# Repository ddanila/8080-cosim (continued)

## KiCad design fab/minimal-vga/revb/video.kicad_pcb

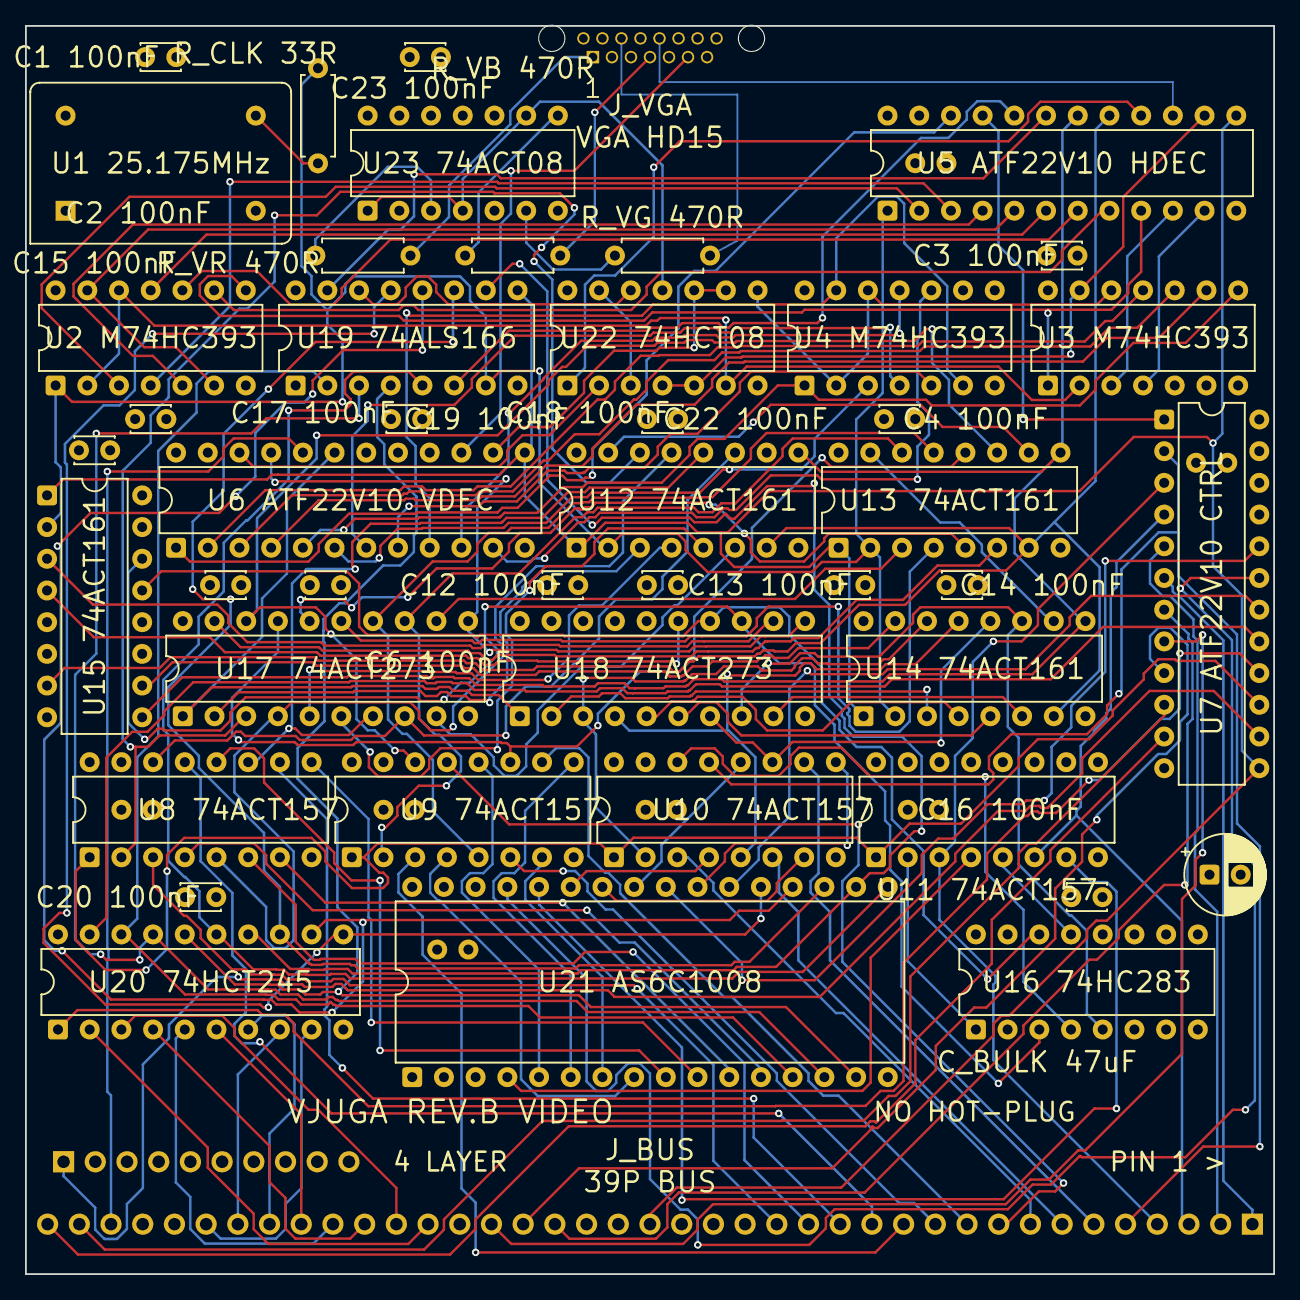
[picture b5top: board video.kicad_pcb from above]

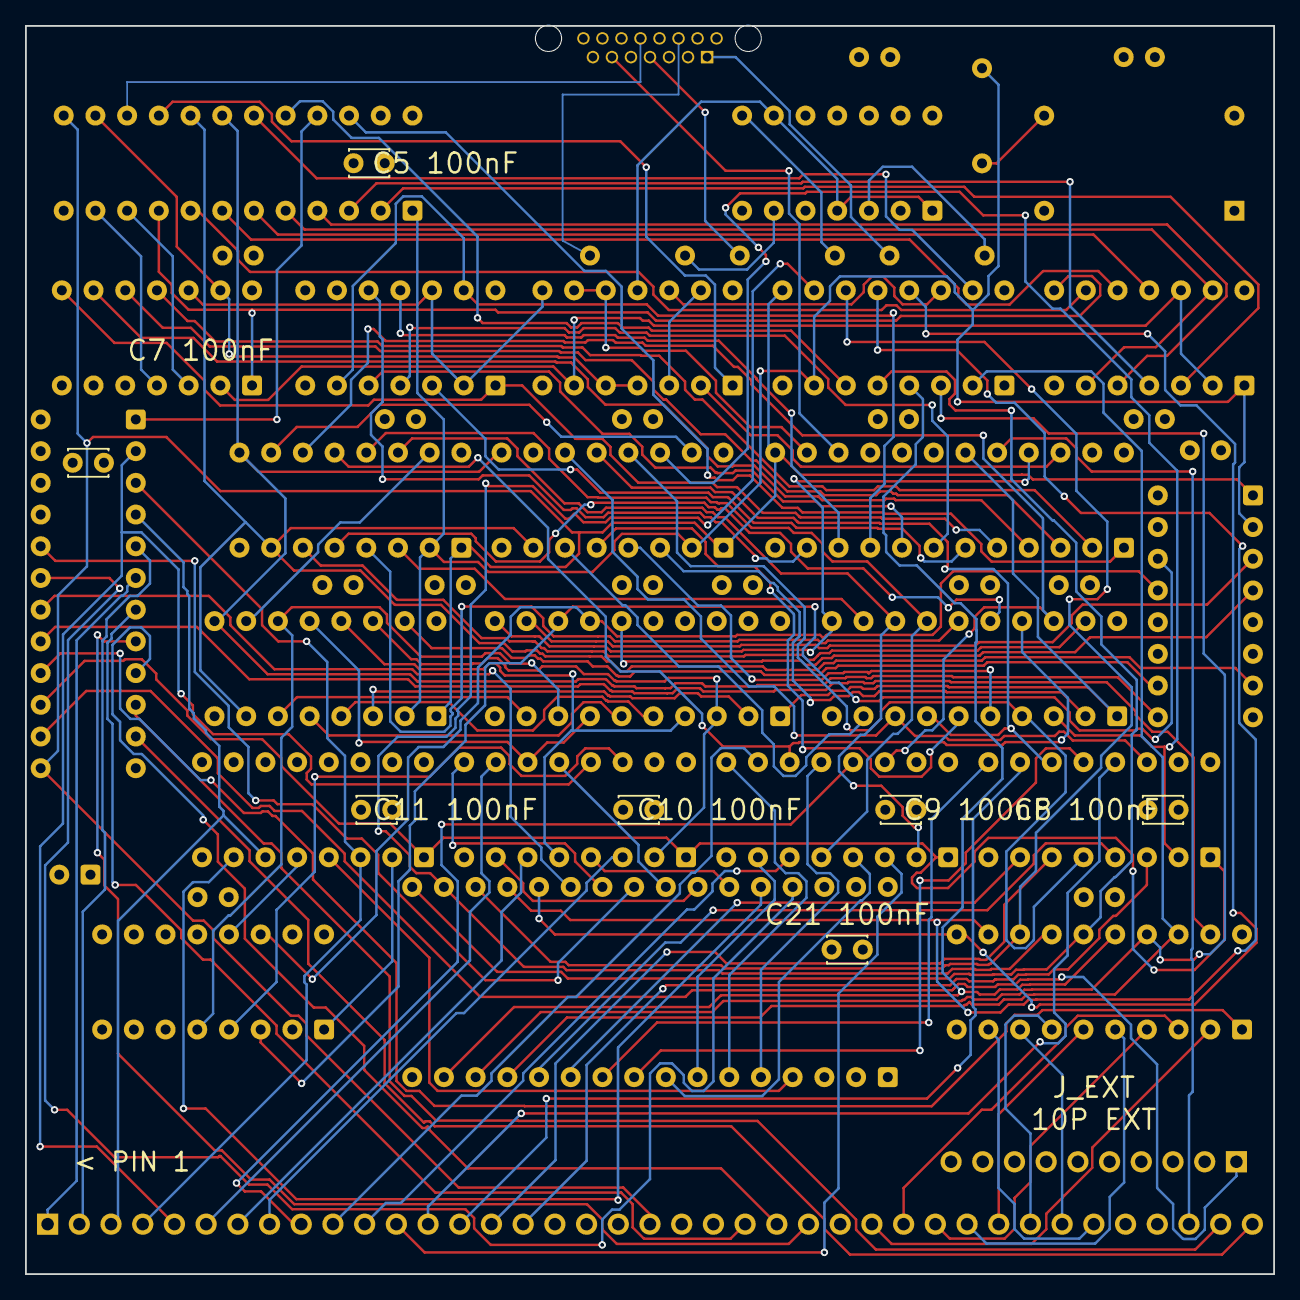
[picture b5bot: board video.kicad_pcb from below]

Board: 4 copper layers, 100.0 x 100.0 mm, 54 parts (8 on the bottom side), 143 nets.

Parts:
C1, C2, C3, C4, C5, C6, C7, C8, C9, C10, C11, C12, C13, C14, C15, C16, C17, C18, C19, C20, C21, C22, C23: C_Disc_D3.0mm_W2.0mm_P2.50mm
C_BULK: CP_Radial_D6.3mm_P2.50mm
J_BUS: PinHeader_1x39_P2.54mm_Horizontal
J_EXT: PinHeader_1x10_P2.54mm_Horizontal
J_VGA: NorComp_200-015-213L537
R_CLK: R_Axial_DIN0207_L6.3mm_D2.5mm_P7.62mm_Horizontal
R_VB: R_Axial_DIN0207_L6.3mm_D2.5mm_P7.62mm_Horizontal
R_VG: R_Axial_DIN0207_L6.3mm_D2.5mm_P7.62mm_Horizontal
R_VR: R_Axial_DIN0207_L6.3mm_D2.5mm_P7.62mm_Horizontal
U1: Oscillator_DIP-14
U2, U3, U4, U22, U23: DIP-14_W7.62mm
U5, U6, U7: DIP-24_W7.62mm
U8, U9, U10, U11, U12, U13, U14, U15, U16, U19: DIP-16_W7.62mm
U17, U18, U20: DIP-20_W7.62mm
U21: DIP-32_W15.24mm

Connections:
A0: J_BUS.16, U8.3
A1: J_BUS.15, U8.6
A2: J_BUS.14, U8.10
A3: J_BUS.13, U8.13
A4: J_BUS.12, U9.3
A5: J_BUS.11, U9.6
A6: J_BUS.10, U9.10
A7: J_BUS.9, U9.13
A8: J_BUS.8, U10.3
A9: J_BUS.7, U10.6
A10: J_BUS.6, U10.10
A11: J_BUS.5, U7.2, U10.13
A12: J_BUS.4, U7.3, U11.3
A13: J_BUS.3, U7.4, U11.6
A14: J_BUS.2, U7.5
A15: J_BUS.1, U7.6
BYTE_TICK: U5.17, U12.7, U13.7, U14.7, U15.7
D0: J_BUS.27, U20.2
D1: J_BUS.28, U20.3
D2: J_BUS.29, U20.4
D3: J_BUS.30, U20.5
D4: J_BUS.31, U20.6
D5: J_BUS.32, U20.7
D6: J_BUS.33, U20.8
D7: J_BUS.34, U20.9
D245_DIR: U7.16, U20.1
D245_OE: U7.17, U20.19
DOTCLK: R_CLK.2, U2.1, U5.1, U12.2, U13.2, U14.2, U15.2, U19.7
DOTCLK_RAW: R_CLK.1, U1.8
FBA11: U10.14, U16.4
FBA12: U11.2, U16.1
FBA13: U11.5, U16.13
FB_CE_N: U7.18, U21.22
FB_OE_N: U7.20, U21.24
FB_WE_N: U7.19, U21.29
FD0: U19.2, U20.18, U21.13
FD1: U19.3, U20.17, U21.14
FD2: U19.4, U20.16, U21.15
FD3: U19.5, U20.15, U21.17
FD4: U19.10, U20.14, U21.18
FD5: U19.11, U20.13, U21.19
FD6: U19.12, U20.12, U21.20
FD7: U19.13, U20.11, U21.21
FETCH: U5.21, U7.1
FI_LOAD_N: U5.18, U12.9, U13.9, U14.9, U15.9
FRAME_TICK: J_BUS.37, U6.20
FRAME_TOP_N: U6.19, U17.1, U18.1
GND: C1.2, C2.2, C3.2, C4.2, C5.2, C6.2, C7.2, C8.2, C9.2, C10.2, C11.2, C12.2, C13.2, C14.2, C15.2, C16.2, C17.2, C18.2, C19.2, C20.2, C21.2, C22.2, C23.2, C_BULK.2, J_BUS.17, J_EXT.10, J_VGA.5, J_VGA.6, J_VGA.7, J_VGA.8, J_VGA.10, U1.7, U2.7, U3.7, U4.7, U5.12, U6.12, U7.12, U8.8, U8.15, U9.8, U9.15, U10.8, U10.15, U11.8, U11.10, U11.11, U11.13, U11.14, U11.15, U12.8, U13.8, U14.8, U15.5, U15.6, U15.8, U16.7, U16.8, U16.11, U16.12, U16.15, U17.10, U18.10, U18.17, U18.18, U19.1, U19.8, U20.10, U21.2, U21.3, U21.16, U21.31, U22.7, U23.7, U23.12, U23.13
HC0: U2.3, U5.2
HC1: U2.4, U5.3
HC2: U2.5, U5.4
HC3: U2.6, U2.13, U5.5
HC4: U2.11, U5.6
HC5: U2.10, U5.7
HC6: U2.9, U5.8
HC7: U2.8, U3.1, U5.9
HC8: U3.3, U5.10
HC9: U3.4, U5.11
HSYNC_N: J_VGA.13, U5.15
HV_ACTIVE: U22.3, U22.13
H_ACTIVE: U5.16, U22.1
H_CLR: U2.2, U2.12, U3.2, U22.6
H_END: U3.13, U5.14, U22.4, U22.5
MODE0: J_BUS.38, U7.10
MODE1: J_BUS.39, U7.11
MREQ_N: J_BUS.23, U7.7
MUX_SEL: U7.15, U8.1, U9.1, U10.1, U11.1
PIXEL: U19.14, U22.12
RB0: U12.3, U17.2
RB1: U12.4, U17.5
RB2: U12.5, U17.6
RB3: U12.6, U17.9
RB4: U13.3, U17.12
RB5: U13.4, U17.15
RB6: U13.5, U17.16
RB7: U13.6, U17.19
RB8: U14.3, U18.2
RB9: U14.4, U18.5
RB10: U14.5, U18.6
RB11: U14.6, U18.9
RB12: U15.3, U18.12
RB13: U15.4, U18.15
RB_CLK: U6.21, U17.11, U18.11
RB_STROBE: U5.22, U6.1
RD_N: J_BUS.25, U7.8
RESET_N: J_BUS.20, U5.13, U6.13, U7.13, U12.1, U13.1, U14.1, U15.1, U19.9
SA0: U8.4, U21.12
SA1: U8.7, U21.11
SA2: U8.9, U21.10
SA3: U8.12, U21.9
SA4: U9.4, U21.8
SA5: U9.7, U21.7
SA6: U9.9, U21.6
SA7: U9.12, U21.5
SA8: U10.4, U21.27
SA9: U10.7, U21.26
SA10: U10.9, U21.23
SA11: U10.12, U21.25
SA12: U11.4, U21.4
SA13: U11.7, U21.28
SI0: U8.2, U12.14, U17.3
SI1: U8.5, U12.13, U17.4
SI2: U8.11, U12.12, U17.7
SI3: U8.14, U12.11, U17.8
SI4: U9.2, U13.14, U17.13
SI5: U9.5, U13.13, U17.14
SI6: U9.11, U13.12, U17.17
SI7: U9.14, U13.11, U17.18
SI8: U10.2, U14.14, U18.3
SI9: U10.5, U14.13, U18.4
SI10: U10.11, U14.12, U18.7
SI11: U14.11, U16.5, U18.8
SI12: U15.14, U16.3, U18.13
SI13: U15.13, U16.14, U18.14
SI_TC0: U12.15, U13.10
SI_TC1: U13.15, U14.10
SI_TC2: U14.15, U15.10
SR_INH: U5.20, U19.6
SR_LOAD_N: U5.19, U19.15
VC0: U3.11, U6.2
VC1: U3.10, U6.3
VC2: U3.9, U6.4
VC3: U3.8, U4.1, U6.5
VC4: U4.3, U6.6
VC5: U4.4, U6.7
VC6: U4.5, U6.8
VC7: U4.6, U4.13, U6.9
VC8: U4.11, U6.10
VC9: U4.10, U6.11
VCC5: C1.1, C2.1, C3.1, C4.1, C5.1, C6.1, C7.1, C8.1, C9.1, C10.1, C11.1, C12.1, C13.1, C14.1, C15.1, C16.1, C17.1, C18.1, C19.1, C20.1, C21.1, C22.1, C23.1, C_BULK.1, J_BUS.18, J_EXT.9, U1.14, U2.14, U3.14, U4.14, U5.24, U6.24, U7.24, U8.16, U9.16, U10.16, U11.16, U12.10, U12.16, U13.16, U14.16, U15.16, U16.2, U16.6, U16.16, U17.20, U18.20, U19.16, U20.20, U21.30, U21.32, U22.14, U23.2, U23.5, U23.10, U23.14
VID_B: J_VGA.3, R_VB.2
VID_B_DRV: R_VB.1, U23.8
VID_G: J_VGA.2, R_VG.2
VID_G_DRV: R_VG.1, U23.6
VID_PIXEL: U22.11, U23.1, U23.4, U23.9
VID_R: J_VGA.1, R_VR.2
VID_R_DRV: R_VR.1, U23.3
VSYNC_N: J_VGA.14, U6.15
V_ACTIVE: U6.22, U22.2
V_CLR: U3.12, U4.2, U4.12, U22.8
V_END: U6.14, U22.9, U22.10
WAIT_N: J_EXT.1, U7.14
WR_N: J_BUS.24, U7.9

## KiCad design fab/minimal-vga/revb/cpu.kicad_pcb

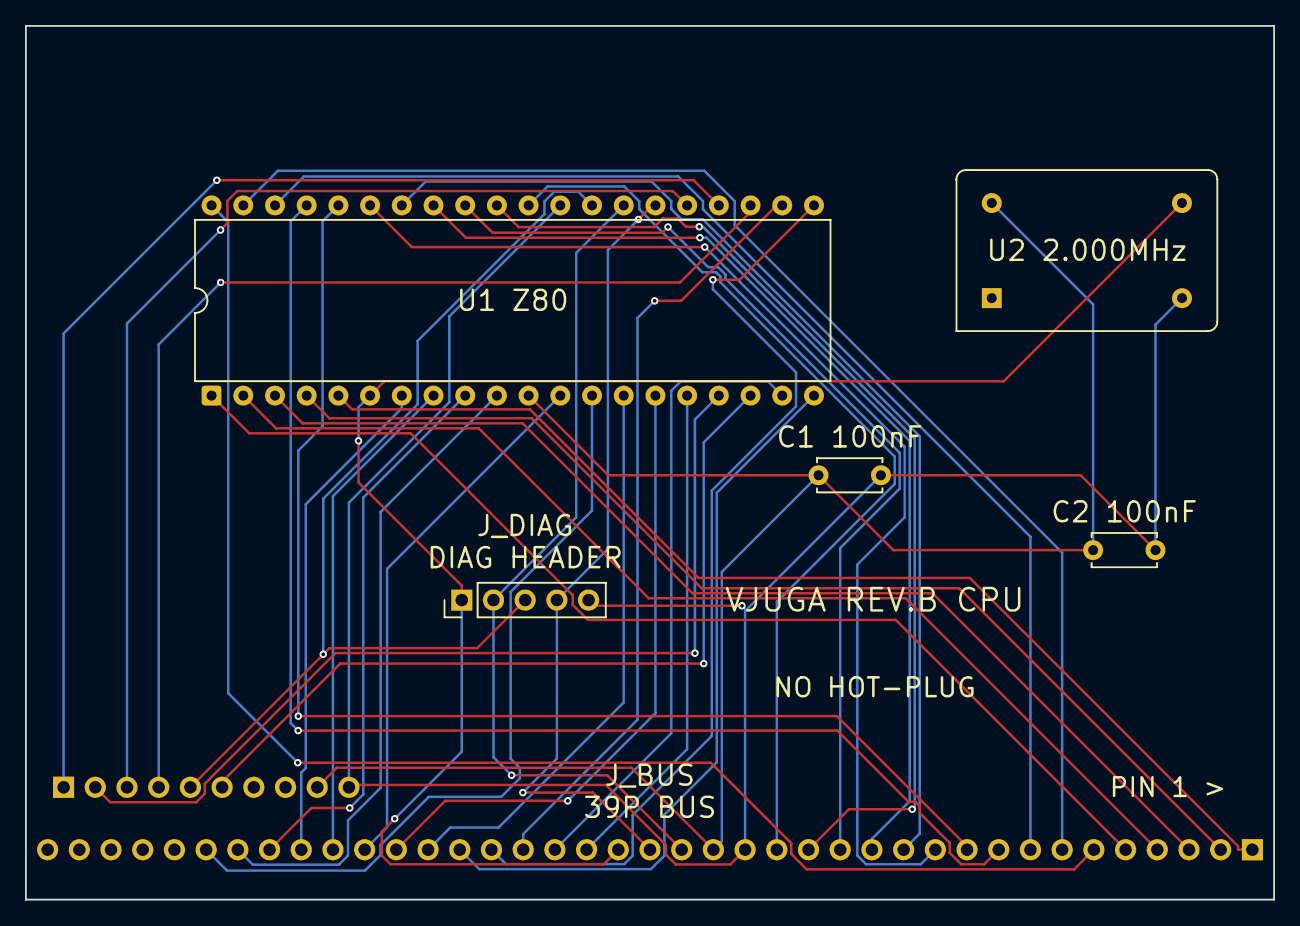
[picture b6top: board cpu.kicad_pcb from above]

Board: 2 copper layers, 100.0 x 70.0 mm, 7 parts (1 on the bottom side), 40 nets.

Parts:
C1, C2: C_Disc_D5.0mm_W2.5mm_P5.00mm
J_BUS: PinHeader_1x39_P2.54mm_Horizontal
J_DIAG: PinHeader_1x05_P2.54mm_Vertical
J_EXT: PinHeader_1x10_P2.54mm_Horizontal
U1: DIP-40_W15.24mm
U2: Oscillator_DIP-14

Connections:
A0: J_BUS.16, U1.30
A1: J_BUS.15, U1.31
A2: J_BUS.14, U1.32
A3: J_BUS.13, U1.33
A4: J_BUS.12, U1.34
A5: J_BUS.11, U1.35
A6: J_BUS.10, U1.36
A7: J_BUS.9, U1.37
A8: J_BUS.8, U1.38
A9: J_BUS.7, U1.39
A10: J_BUS.6, U1.40
A11: J_BUS.5, U1.1
A12: J_BUS.4, U1.2
A13: J_BUS.3, U1.3
A14: J_BUS.2, U1.4
A15: J_BUS.1, U1.5
BUSAK_N: J_EXT.4, U1.23
BUSRQ_N: J_EXT.3, U1.25
CLK: J_BUS.21, J_DIAG.1, U1.6, U2.8
D0: J_BUS.27, U1.14
D1: J_BUS.28, U1.15
D2: J_BUS.29, U1.12
D3: J_BUS.30, U1.8
D4: J_BUS.31, U1.7
D5: J_BUS.32, U1.9
D6: J_BUS.33, U1.10
D7: J_BUS.34, U1.13
GND: C1.2, C2.2, J_BUS.17, J_DIAG.5, J_EXT.10, U1.29, U2.7
HALT_N: J_EXT.6, U1.18
INT_N: J_BUS.22, U1.16
IORQ_N: J_BUS.26, U1.20
M1_N: J_BUS.19, J_DIAG.2, U1.27
MREQ_N: J_BUS.23, U1.19
NMI_N: J_EXT.2, U1.17
RD_N: J_BUS.25, U1.21
RESET_N: J_BUS.20, J_DIAG.4, U1.26
RFSH_N: J_DIAG.3, J_EXT.5, U1.28
VCC5: C1.1, C2.1, J_BUS.18, J_EXT.9, U1.11, U2.14
WAIT_N: J_EXT.1, U1.24
WR_N: J_BUS.24, U1.22

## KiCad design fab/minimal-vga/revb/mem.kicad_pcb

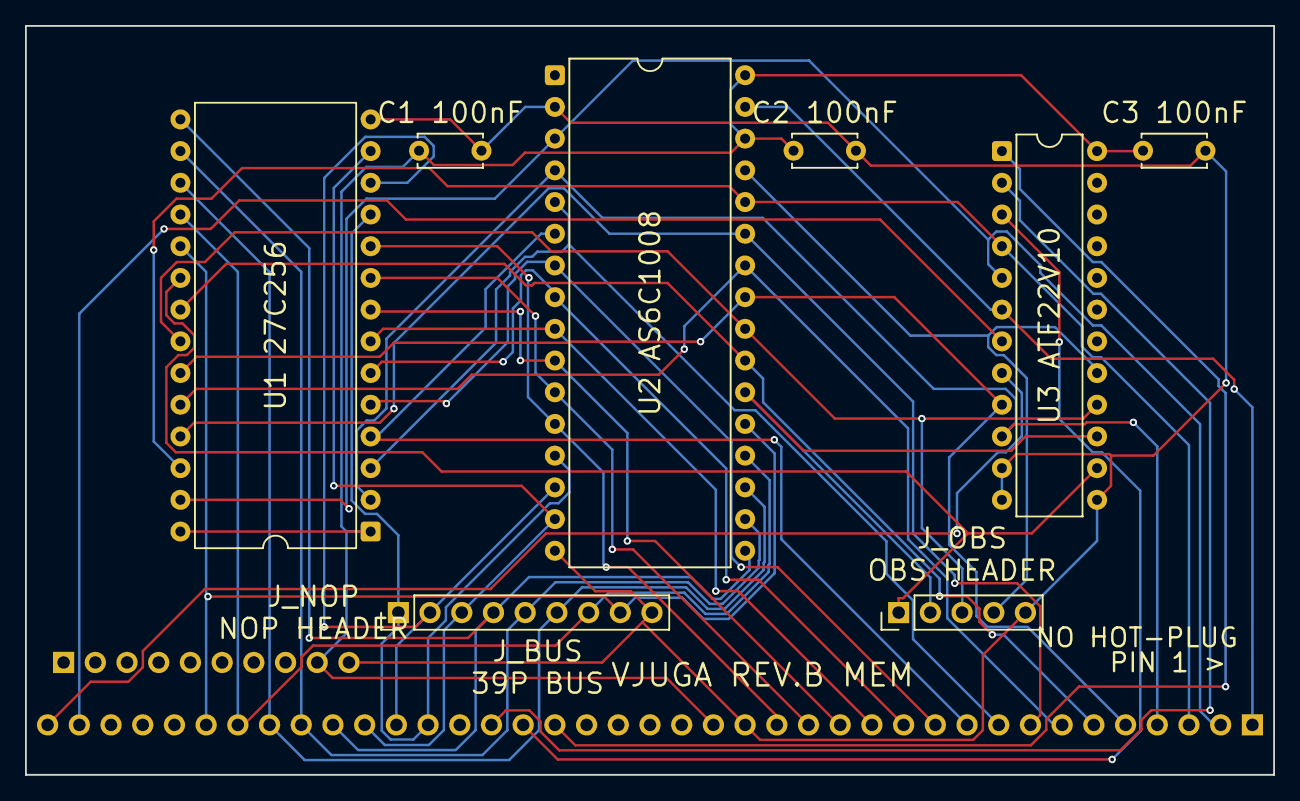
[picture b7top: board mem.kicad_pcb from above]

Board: 2 copper layers, 100.0 x 60.0 mm, 10 parts (1 on the bottom side), 35 nets.

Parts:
C1, C2, C3: C_Disc_D5.0mm_W2.5mm_P5.00mm
J_BUS: PinHeader_1x39_P2.54mm_Horizontal
J_EXT: PinHeader_1x10_P2.54mm_Horizontal
J_NOP: PinHeader_1x09_P2.54mm_Vertical
J_OBS: PinHeader_1x05_P2.54mm_Vertical
U1: DIP-28_W15.24mm
U2: DIP-32_W15.24mm
U3: DIP-24_W7.62mm

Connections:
A0: J_BUS.16, U1.10, U2.12
A1: J_BUS.15, U1.9, U2.11
A2: J_BUS.14, U1.8, U2.10
A3: J_BUS.13, U1.7, U2.9
A4: J_BUS.12, U1.6, U2.8
A5: J_BUS.11, U1.5, U2.7
A6: J_BUS.10, U1.4, U2.6
A7: J_BUS.9, U1.3, U2.5
A8: J_BUS.8, U1.25, U2.27
A9: J_BUS.7, U1.24, U2.26
A10: J_BUS.6, U1.21, U2.23
A11: J_BUS.5, U1.23, U2.25, U3.9
A12: J_BUS.4, U1.2, U2.4, U3.10
A13: J_BUS.3, U1.26, U2.28, U3.4
A14: J_BUS.2, U1.27, U2.3, U3.5
A15: J_BUS.1, U2.31, U3.6
D0: J_BUS.27, J_NOP.1, U1.11, U2.13
D1: J_BUS.28, J_NOP.2, U1.12, U2.14
D2: J_BUS.29, J_NOP.3, U1.13, U2.15
D3: J_BUS.30, J_NOP.4, U1.15, U2.17
D4: J_BUS.31, J_NOP.5, U1.16, U2.18
D5: J_BUS.32, J_NOP.6, U1.17, U2.19
D6: J_BUS.33, J_NOP.7, U1.18, U2.20
D7: J_BUS.34, J_NOP.8, U1.19, U2.21
GND: C1.2, C2.2, C3.2, J_BUS.17, J_EXT.10, J_NOP.9, J_OBS.5, U1.14, U2.2, U2.16, U3.11, U3.12, U3.13
MEM_RD_N: J_OBS.3, U1.22, U2.24, U3.16
MEM_WR_N: J_OBS.4, U2.29, U3.17
MODE0: J_BUS.38, U3.7
MODE1: J_BUS.39, U3.8
MREQ_N: J_BUS.23, U3.1
RAM_CE_N: J_OBS.2, U2.22, U3.15
RD_N: J_BUS.25, U3.2
ROM_CE_N: J_OBS.1, U1.20, U3.14
VCC5: C1.1, C2.1, C3.1, J_BUS.18, J_EXT.9, U1.1, U1.28, U2.30, U2.32, U3.24
WR_N: J_BUS.24, U3.3

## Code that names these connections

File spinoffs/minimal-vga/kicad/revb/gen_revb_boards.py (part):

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mating = json.loads((HERE / "mating.json").read_text())

# ---- accurate DIP pinouts (pin number -> net/function) ----
# Z80 DIP-40: transcribed verbatim from spinoffs/minimal-vga/kicad/rev-a-physical.board.json U1
# (rev A's authoritative Z80 mapping). BUSACK_N/NMI_N map to the rev B bus names.
Z80 = {
    "1":"A11","2":"A12","3":"A13","4":"A14","5":"A15","6":"CLK","7":"D4","8":"D3",
    "9":"D5","10":"D6","11":"VCC5","12":"D2","13":"D7","14":"D0","15":"D1","16":"INT_N",
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    "25":"A8","26":"A13","27":"A14","28":"VCC5",
}
# AS6C1008 DIP-32 (128K x 8 SRAM), Alliance Memory datasheet pinout.  Pin 1 is
# NC; pin 30 is the active-HIGH CE2.  The rev-B Memory card uses A0..A15, holds
# A16 low, and holds CE2 high.
SRAM_128K = {
    "1":"RAM_PIN1_NC","2":"GND","3":"A14","4":"A12","5":"A7","6":"A6","7":"A5","8":"A4",
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
# --- B3-tier parts (D1.26): footprinted AND fully wired on the io card, but DNP so
# B3 is populate-only, no respin. ---
# 82C55 PPI DIP-40. PA0-7 = keyboard columns; PB0-3 <- 74148 encoder; PC0/PC1 = the
# memory-overlay mode bits (bus MODE0/MODE1). Ports 0x04-0x07 via PPI_CS_N.
PPI_8255 = {
    "1":"KBD_COL3","2":"KBD_COL2","3":"KBD_COL1","4":"KBD_COL0","5":"RD_N","6":"PPI_CS_N",
    "7":"GND","8":"A1","9":"A0","10":"PC7_NC","11":"PC6_NC","12":"PC5_NC","13":"PC4_NC",
    "14":"MODE0","15":"MODE1","16":"PC2_NC","17":"PC3_NC",
    "18":"KBD_ENC0","19":"KBD_ENC1","20":"KBD_ENC2","21":"KBD_ENC_GS",
    "22":"PB4_NC","23":"PB5_NC","24":"PB6_NC","25":"PB7_NC","26":"VCC5",
    "27":"D7","28":"D6","29":"D5","30":"D4","31":"D3","32":"D2","33":"D1","34":"D0",
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ENC_74148 = {
    "1":"KBD_ROW4","2":"KBD_ROW5","3":"KBD_ROW6","4":"KBD_ROW7","5":"KBD_ENC_GS","6":"KBD_ENC2",
    "7":"KBD_ENC1","8":"GND","9":"KBD_ENC0","10":"KBD_ROW0","11":"KBD_ROW1","12":"KBD_ROW2",
    "13":"KBD_ROW3","14":"GND","15":"KBD_ENC_EO_NC","16":"VCC5",   # pin14 EI tied active
}
# 8259-class PIC DIP-28. Ports 0x00-0x01 via PIC_CS_N. IR wiring per hdl/juku_top.v:
# ir0=FDC INTRQ, ir1=FDC DRQ, ir2=serial RxRDY, ir3=serial TxRDY, ir5=frame tick.
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    "8":"HC6","9":"HC7","10":"HC8","11":"HC9","12":"GND","13":"RESET_N","14":"H_END",
    "15":"HSYNC_N","16":"H_ACTIVE","17":"BYTE_TICK","18":"FI_LOAD_N","19":"SR_LOAD_N",
    "20":"SR_INH","21":"FETCH","22":"RB_STROBE","23":"VID_HDEC_O23_NC","24":"VCC5"}
# U6 pin 1 is the ATF22V10 global clock.  HDEC's one-dot RB_STROBE clocks the
# registered modulo-six frame divider once per line; the D equations hold except
# at VC=524.  Pin 13 supplies synchronous reset and combinatorial reset gating.
GAL22V10_VDEC = {"1":"RB_STROBE","2":"VC0","3":"VC1","4":"VC2","5":"VC3","6":"VC4","7":"VC5",
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    # window decode + WAIT contention (D2.5). ----
    "video": [
        # The full-can oscillator has fast TTL edges.  A 33-ohm source resistor sits
        # immediately at pin 8 before the seven-load on-card DOTCLK tree (R5.V5).
        comp("U1", "OSC_25M175", {"1": "OSC_EN_NC", "7": "GND", "8": "DOTCLK_RAW", "14": "VCC5"}),
        comp("R_CLK", "R_33", {"1": "DOTCLK_RAW", "2": "DOTCLK"}),
        # '393 dot/line counters (chained): HC0-9, VC0-9; MR = end-of-line/frame
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
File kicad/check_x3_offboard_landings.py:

#!/usr/bin/python3
"""Guard X3 cable landings and the sheet-1 triple D104 receiver."""
from __future__ import annotations

import json
from pathlib import Path

import pcbnew


ROOT = Path(__file__).resolve().parents[1]
BOARD = ROOT / "kicad/juku.kicad_pcb"
SPEC = ROOT / "kicad/juku.board.json"
SIGNALS = {22: "S_OC", 23: "S_TTL", 24: "S_SIN", 25: "S_CTS", 26: "S_DSR",
           29: "S_SOUT", 30: "S_RTS", 31: "S_DTP", 32: "S_OC"}


def mm(value: int) -> float:
    return pcbnew.ToMM(value)


def main() -> int:
    board = pcbnew.LoadBoard(str(BOARD))
    spec = json.loads(SPEC.read_text(encoding="utf-8"))
    failures: list[str] = []
    if board.FindFootprintByReference("X3") is not None:
        failures.append("off-board X3 still has a PCB footprint")
    for number in range(21, 33):
        refdes = f"A{number}"
        footprint = board.FindFootprintByReference(refdes)
        pad = footprint.FindPadByNumber("1") if footprint else None
        if pad is None:
            failures.append(f"{refdes}.1 is missing")
            continue
        position = pad.GetPosition()
        expected_x = 173.7 + (number - 21) * 2.54
        if abs(mm(position.x) - expected_x) > 0.002 or abs(mm(position.y) - 15.2) > 0.002:
            failures.append(f"{refdes}.1 has wrong position")
        net = SIGNALS.get(number, f"X3_HARNESS_{number - 20}")
        if pad.GetNetname() != net:
            failures.append(f"{refdes}.1 net {pad.GetNetname()!r} != {net!r}")
        nodes = {tuple(node) for node in spec["nets"][net]["nodes"]}
        if ("X3", str(number - 20)) not in nodes:
            failures.append(f"{net} lacks X3.{number - 20}")
    for net in ("X3_HARNESS_7", "X3_HARNESS_8"):
        record = spec["nets"][net]
        if record.get("intentional_harness_only") is not True or len(record["nodes"]) != 2:
            failures.append(f"{net} is not a two-end intentional cable-only contact")

    d104 = board.FindFootprintByReference("D104")
    expected_d104 = {"4": "S_SIN", "13": "SER_RXD", "5": "S_CTS",
                     "12": "SER_CTS_N", "6": "S_DSR", "11": "SER_DSR_N",
                     "8": "GND", "15": "P5V"}
    for pin, net in expected_d104.items():
        pad = d104.FindPadByNumber(pin) if d104 else None
        if pad is None or pad.GetNetname() != net:
            failures.append(f"D104.{pin} is not assigned to {net}")
    d11 = board.FindFootprintByReference("D11")
    for pin, net in {"17": "SER_CTS_N", "22": "SER_DSR_N"}.items():
        pad = d11.FindPadByNumber(pin) if d11 else None
        if pad is None or pad.GetNetname() != net:
            failures.append(f"D11.{pin} is not assigned to {net}")
    r101 = board.FindFootprintByReference("R101")
    for pin, net in {"1": "X3_HARNESS_1", "2": "P5V"}.items():
        pad = r101.FindPadByNumber(pin) if r101 else None
        if pad is None or pad.GetNetname() != net:
            failures.append(f"R101.{pin} is not assigned to {net}")
    if r101 is not None and r101.GetValue() != "120":
        failures.append("R101 value is not 120 ohms")
    for refdes, pad_targets in {
        "R104": {"1": (213.935, 59.309, "X2_IRQ0"), "2": (213.935, 69.469, "P5V")},
        "R18": {"1": (211.299, 70.945, "S_OC"), "2": (211.654, 81.099, "SER_TXD")},
    }.items():
        footprint = board.FindFootprintByReference(refdes)
        for pin, (x, y, net) in pad_targets.items():
            pad = footprint.FindPadByNumber(pin) if footprint else None
            if pad is None or pad.GetNetname() != net:
                failures.append(f"{refdes}.{pin} is not assigned to {net}")
            elif abs(pcbnew.ToMM(pad.GetPosition().x) - x) > 0.3 or abs(pcbnew.ToMM(pad.GetPosition().y) - y) > 0.3:
                failures.append(f"{refdes}.{pin} is outside its registered owner-photo hole site")
    modeled = {chip["ref"]: chip for chip in spec["chips"]}
    if modeled.get("R101", {}).get("value") != "120":
        failures.append("source-model R101 is not 120 ohms")
    if modeled.get("R104", {}).get("value") != "470" or modeled.get("R104", {}).get("pcb_placement_pending"):
        failures.append("source-model R104 must be 470 ohms and placed")
    for refdes, expected in {
        "D12": {"5": "X2_IRQ0", "6": "INT4_RAW", "7": "INT4_RAW"},
        "X1": {"114C": "INT4_RAW"},
    }.items():
        footprint = board.FindFootprintByReference(refdes)
        for pin, net in expected.items():
            pad = footprint.FindPadByNumber(pin) if footprint else None
            if pad is None or pad.GetNetname() != net:
                failures.append(f"{refdes}.{pin} is not assigned to {net}")
    for refdes, expected in {
        "R18": {"1": "S_OC", "2": "SER_TXD"},
        "R30": {"1": "S_OC", "2": "GND"},
    }.items():
        footprint = board.FindFootprintByReference(refdes)
        for pin, net in expected.items():
            pad = footprint.FindPadByNumber(pin) if footprint else None
            if pad is None or pad.GetNetname() != net:
                failures.append(f"{refdes}.{pin} is not assigned to {net}")
        if footprint is not None and footprint.GetValue() != "33к":
            failures.append(f"{refdes} value is not the native 33к literal")
    for refdes, expected in {
        "D3": {"9": "SER_TXD", "8": "SER_TXD_INV"},
        "D12": {"1": "SER_TXD_INV", "2": "SER_TXD_INV", "3": "S_OC"},
    }.items():
        footprint = board.FindFootprintByReference(refdes)
        for pin, net in expected.items():
            pad = footprint.FindPadByNumber(pin) if footprint else None
            if pad is None or pad.GetNetname() != net:
                failures.append(f"{refdes}.{pin} is not assigned to {net}")

    if failures:
        for failure in failures:
            print("FAIL:", failure)
        return 1
    print("X3 LANDINGS: PASS — A21..A32 harness and D104 triple receiver")
    return 0


if __name__ == "__main__":
    raise SystemExit(main())

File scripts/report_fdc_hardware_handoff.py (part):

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        failures.append("D96 section-2 isolated-/Q constraint is absent")
    d96_toggle_closed = (
        {"D96.2", "D96.6"}
        == {f"{ref}.{pin}" for ref, pin in net(board, "D96_TOGGLE_FEEDBACK").get("nodes", [])}
        and all(has_node(board, "WREQ_N", "D96", pin) for pin in ("1", "4"))
        and has_node(board, "FDC_IRQ_CONDITIONED_N", "D96", "10")
        and has_node(board, "FDC_IRQ_CONDITIONED_N", "D96", "12")
        and has_node(board, "D94_D1_D99_A2N", "D96", "11")
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        failures.append("factory-proved D106-D28-D96-D93 recovered-clock chain is absent")
    d106_closed = (
        {"D106.1", "D106.5", "D106.9", "D106.10", "D106.15", "R78.1"}
        == {f"{ref}.{pin}" for ref, pin in net(board, "D106_PRESET_HIGH").get("nodes", [])}
        and has_node(board, "P5V", "R78", "2")
        and has_node(board, "FDC_SEPARATOR_CLOCK", "D106", "4")
        and has_node(board, "FDC_RAW_READ", "D106", "11")
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    if (
        not has_node(board, "D93_TEST_WF_VFOE", "D93", "22")
        or not has_node(board, "D93_TEST_WF_VFOE", "D93", "33")
        or len(net(board, "D93_TEST_WF_VFOE").get("nodes", [])) != 2
    ):
        failures.append("sheet-3 D93 TEST-to-WF/VFOE local tie is absent or has extra endpoints")
    if (
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            "  corroboration. The `.092` table is physically captured.",
            "- Before real FDC bring-up, confirm physical D96.9 Q2-to-D101 A0-A3",
            "  continuity, D96.11 CLK2-to-D94.2/D99.9 continuity, and the source-drawn",
            "  D96.13 /CLR2-to-D99.10 B2 join; identify the shared clear/B2 source separately. Capture WREQ_N at pins1/4 with Q1/pin5",
            "  and /Q1/pin6 because simultaneous async release leaves restart phase",
            "  undefined. Check the photographed D96.11-to-D28.11/DRQ candidate",
            "  against the separate source nets; D96.9's onward physical route remains",
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
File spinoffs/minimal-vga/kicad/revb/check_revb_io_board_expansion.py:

#!/usr/bin/env python3
"""R5.I4 independent generated-board/pin closure and mutation controls."""
from __future__ import annotations

import copy
import json
import sys
from pathlib import Path


HERE = Path(__file__).resolve().parent


def validate(board: dict, contract: dict) -> list[str]:
    errors: list[str] = []
    parts = {part["ref"]: part for part in board["chips"]}

    def exact(ref: str, pins: dict[str, str], typ: str) -> None:
        part = parts.get(ref)
        if part is None:
            errors.append(f"missing {ref}")
        elif part["type"] != typ or part["pins"] != pins:
            errors.append(f"{ref} type/pin map differs from frozen contract")

    exact("U2", contract["decode_gal"]["pins"], "GAL22V10_IOSEL")
    exact("U8", contract["timer"]["pins"], "PIT_8253")
    exact("U9", contract["post"]["latch_pins"], "ACT_273_POST")
    if parts.get("U7", {}).get("pins", {}).get("4") != "PIT_CLK0":
        errors.append("U7 /4 is not routed to PIT_CLK0")
    for ref, wanted in contract["baud_tree"]["jumpers"].items():
        if parts.get(ref, {}).get("pins") != wanted["pins"]:
            errors.append(f"{ref} does not implement frozen two-stage clock selection")

    if any(parts.get(ref, {}).get("dnp") for ref in ("U4", "U5", "U6")):
        errors.append("C10-capable PPI/PIC/encoder remains DNP")
    for ref in ("U1", "U2", "U3", "U4", "U5", "U6", "U7", "U8", "U9"):
        if ref not in parts:
            errors.append(f"missing populated digital package {ref}")
    for i in range(1, 10):
        if parts.get(f"C{i}", {}).get("pins") != {"1": "VCC5", "2": "GND"}:
            errors.append(f"C{i} is not the local VCC/GND 100 nF allowance")

    for bit in range(8):
        if parts.get(f"R_POST{bit}", {}).get("pins") != {
                "1": f"POST_Q{bit}", "2": f"POST_LED{bit}_A"}:
            errors.append(f"POST bit {bit} resistor path wrong")
        if parts.get(f"D_POST{bit}", {}).get("pins") != {
                "1": "GND", "2": f"POST_LED{bit}_A"}:
            errors.append(f"POST bit {bit} LED polarity wrong")
    sound = {
        "Q1": {"1": "GND", "2": "SOUND_BASE", "3": "SOUND_LOW"},
        "BZ1": {"1": "VCC5", "2": "SOUND_LOW"},
        "J_SOUND": {"1": "VCC5", "2": "SOUND_LOW"},
        "R_SOUND_BASE": {"1": "PIT_SOUND", "2": "SOUND_BASE"},
        "R_SOUND_PD": {"1": "SOUND_BASE", "2": "GND"},
    }
    for ref, pins in sound.items():
        if parts.get(ref, {}).get("pins") != pins:
            errors.append(f"sound path {ref} wrong")
    tp = parts.get("J_PIT_TP", {}).get("pins", {})
    if set(tp.values()) != {"PIT_CLK0", "PIT_BAUD", "PIT_SOUND", "PIT_OUT2_TP", "GND"}:
        errors.append("PIT test header omits a frozen clock/output/GND")

    # Every declared net must be the exact inverse of the package pin maps.
    derived: dict[str, list[list[str]]] = {}
    for part in board["chips"]:
        for pin, net in part["pins"].items():
            derived.setdefault(net, []).append([part["ref"], pin])
    recorded = {net: row["nodes"] for net, row in board["nets"].items()}
    if derived != recorded:
        errors.append("board nets are stale relative to package pins")
    return errors


def main() -> int:
    contract = json.loads((HERE / "io-expansion.json").read_text())
    board = json.loads((HERE / "io.board.json").read_text())
    errors = validate(board, contract)
    if "--self-test" in sys.argv:
        mutations = []
        for ref, pin, net in (("U8", "9", "BAUD_DIV2_NC"),
                              ("U8", "21", "UART_CS_N"),
                              ("U9", "11", "PIT_CS_N"),
                              ("Q1", "1", "SOUND_LOW"),
                              ("D_POST7", "1", "POST_LED7_A")):
            changed = copy.deepcopy(board)
            next(part for part in changed["chips"] if part["ref"] == ref)["pins"][pin] = net
            # Rebuild nets so each mutation tests the electrical contract rather than
            # merely the board.json inverse-net consistency check.
            nets: dict[str, list[list[str]]] = {}
            for part in changed["chips"]:
                for p, n in part["pins"].items(): nets.setdefault(n, []).append([part["ref"], p])
            changed["nets"] = {n: {"nodes": nodes} for n, nodes in nets.items()}
            mutations.append(bool(validate(changed, contract)))
        if not all(mutations):
            errors.append("one or more PIT/POST/sound mutation controls escaped")
    if errors:
        print("rev B expanded I/O board check FAILED:")
        for error in errors: print(f"- {error}")
        return 1
    print("rev B expanded I/O board PASS: U1-U9 populated, exact PIT/GAL/POST pins, clocks, LEDs, sound, decoupling and five mutations")
    return 0


if __name__ == "__main__":
    raise SystemExit(main())

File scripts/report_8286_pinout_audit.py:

#!/usr/bin/env python3
"""Guard the physical 8286 pinout and D4/D107 routed channel assignments."""
from __future__ import annotations

import json
from pathlib import Path

ROOT = Path(__file__).resolve().parents[1]
BOARD = ROOT / "kicad/juku.board.json"
MAP = ROOT / "sync/map.json"
OUT = ROOT / "docs/8286-pinout-audit.md"

PHYSICAL = {
    **{str(pin): f"AIN{pin - 1}" for pin in range(1, 9)},
    "9": "OE_N",
    "11": "T",
    **{str(pin): f"AOUT{19 - pin}" for pin in range(12, 20)},
}
PHYSICAL_D100 = {
    **{str(pin): f"A{pin - 1}" for pin in range(1, 9)},
    "9": "OE_N", "10": "VSS_GND", "11": "T",
    **{str(pin): f"B{19 - pin}" for pin in range(12, 20)},
    "20": "VCC_5V",
}

EXPECTED_NET_PINS = {
    "D107": {**{f"A{i}": str(i + 1) for i in range(8)},
             **{f"BA{i}": str(19 - i) for i in range(8)}},
    "D4": {
        "A8": "8", "A9": "7", "A10": "1", "A11": "2",
        "A12": "5", "A13": "4", "A14": "3", "A15": "6",
        "BA8": "12", "BA9": "13", "BA10": "19", "BA11": "18",
        "BA12": "15", "BA13": "16", "BA14": "17", "BA15": "14",
    },
    "D23": {**{f"BA{i}": str(i + 1) for i in range(8)},
            **{f"ADR{i}_N": str(19 - i) for i in range(8)}},
    "D24": {**{f"BA{i + 8}": str(i + 1) for i in range(8)},
            **{f"ADR{'89ABCDEF'[i]}_N": str(19 - i) for i in range(8)}},
    "D25": {**{f"DB{i}": str(i + 1) for i in range(8)},
            **{f"DAT{i}_N": str(19 - i) for i in range(8)}},
    "D100": {
        "FDC_DIR_TO_D100": "1", "FDC_STEP_TO_D100": "2",
        "FDC_HLD_TO_D100": "3", "FDC_TG43_TO_D100": "4",
        "FDC_WG_TO_D100": "5", "FDC_PRECOMP_WRDATA": "6",
        "D99_Q2_BOUNDARY": "7", "FDC_SIDE_SEL": "8",
        "D99_Q2N_BOUNDARY": "9", "D100_CONTROL_SHEET1_BOUNDARY": "11",
        "X4_SIDE_SEL": "12", "X4_MOTOR_ON_N": "13",
        "X4_WR_DATA_N": "14", "X4_WR_GATE_N": "15",
        "X4_TG43": "16", "X4_HLOAD_N": "17",
        "X4_STEP_N": "18", "X4_DIR_N": "19",
    },
}


def main() -> None:
    board = json.loads(BOARD.read_text())
    mapping = json.loads(MAP.read_text())
    chips = {chip["ref"]: chip for chip in board["chips"]}
    endpoint_net = {}
    for name, entry in board["nets"].items():
        nodes = entry.get("nodes", []) if isinstance(entry, dict) else entry
        for ref, pin in nodes:
            endpoint_net[(ref, str(pin))] = name

    checks = []
    for ref in ("D4", "D107", "D23", "D24", "D25"):
        actual = {pin: name for pin, name in chips[ref]["pins"].items() if pin in PHYSICAL}
        checks.append((f"{ref} uses the Intel DIP-20 logical pin names", actual == PHYSICAL))
        expected = EXPECTED_NET_PINS[ref]
        observed = {net: endpoint_net.get((ref, pin)) for net, pin in expected.items()}
        checks.append((f"{ref} channel pad assignments match sheet 1", observed == {n: n for n in expected}))

    d29_actual = {pin: name for pin, name in chips["D29"]["pins"].items() if pin in PHYSICAL}
    checks.append(("D29 uses the Intel DIP-20 logical pin names", d29_actual == PHYSICAL))
    d29_exact_source = {
        "1": "PHI2TTL", "2": "AMW_N", "3": "INHIB_STATUS_BOUNDARY",
        "4": "IORD", "5": "IOWR", "6": "MEMR", "7": "D30_Q2N_D29_AIN7",
        "8": "MEMW", "12": "AMWC_N", "13": "MWC_N", "14": "MRC_N",
        "15": "IOWC_N", "16": "IORC_N", "17": "INHIB_N", "18": "IOM_N",
        "19": "CCLCK",
    }
    checks.append((
        "D29 physical input/output pads match all eight exact .009 sheet-1 rows",
        {pin: endpoint_net.get(("D29", pin)) for pin in d29_exact_source}
        == d29_exact_source,
    ))

    d100 = chips["D100"]
    checks.append(("D100 uses the Intel 8287 DIP-20 pin names", d100["pins"] == PHYSICAL_D100))
    d100_expected = EXPECTED_NET_PINS["D100"]
    d100_observed = {key: endpoint_net.get(("D100", pin)) for key, pin in d100_expected.items()}
    d100_expected_nets = {key: key for key in d100_expected}
    checks.append(("D100 drive-interface pad assignments follow factory sheet 3", d100_observed == d100_expected_nets))

    type_map = mapping["pinmaps"]["kicad"]["BUF8286"]
    checks.append(("LVS type pinmap follows A0-A7 pins 1-8 and B0-B7 pins 19-12", type_map == PHYSICAL))
    vabus_map = mapping["pinmaps"]["kicad"]["VABUS"]
    checks.append(("8287 LVS type pinmap follows the same physical channel pairs", vabus_map == PHYSICAL))
    checks.append(("D100 LVS pinmap follows the complete 8287 contract", mapping["pinmaps"]["kicad"]["BUF8287"] == PHYSICAL_D100))
    d4_map = mapping["pinmaps"]["kicad_instance"]["D4"]
    expected_d4_map = {
        pin: f"AIN{i}" for i, pin in enumerate(("8", "7", "1", "2", "5", "4", "3", "6"))
    }
    expected_d4_map.update({
        pin: f"AOUT{i}" for i, pin in enumerate(("12", "13", "19", "18", "15", "16", "17", "14"))
    })
    checks.append(("D4 LVS override preserves its source high-address permutation", d4_map == expected_d4_map))
    d29_map = mapping["pinmaps"]["kicad_instance"]["D29"]
    expected_d29_map = {
        pin: f"AIN{i}" for i, pin in enumerate(("3", "1", "2", "7", "6", "8", "4", "5"))
    }
    expected_d29_map.update({
        pin: f"AOUT{i}" for i, pin in enumerate(("17", "19", "18", "13", "14", "12", "16", "15"))
    })
    checks.append(("D29 LVS override preserves its source command permutation", d29_map == expected_d29_map))
    checks.append((
        "D7 pin 5 and D29 physical A2 pin 3 share the traced -INHIB source boundary",
        {
            (ref, str(pin))
            for ref, pin in board["nets"]["INHIB_STATUS_BOUNDARY"]["nodes"]
        } == {("D7", "5"), ("D29", "3")},
    ))
    checks.append((
        "D7 pin 4 and D29 physical pin 8 share the exact -MWR conductor",
        {("D7", "4"), ("D29", "8")} <= {
            (ref, str(pin))
            for ref, pin in board["nets"]["MEMW"]["nodes"]
        },
    ))
    checks.append((
        "D7 pin 3 joins D29 physical pin 2 but remains separate from qualified /WR",
        {("D7", "3"), ("D29", "2")} <= {
            (ref, str(pin))
            for ref, pin in board["nets"]["AMW_N"]["nodes"]
        }
        and endpoint_net.get(("D105", "3")) == "IOWR",
    ))

    failed = [name for name, ok in checks if not ok]

    lines = [
        "# 8286 transceiver pinout audit", "",
        "Status: **PINOUT AUDIT FAILED**" if failed
        else "Status: **PHYSICAL PINOUT GUARDED**", "",
        "The original Intel `M8286/M8287 Octal Bus Transceiver` datasheet assigns",
        "A0-A7 to DIP pins 1-8 and the paired B0-B7 channels to pins 19-12.",
        "Sheet 1 routes D107 and D23-D25 straight, permutes D4's high-address",
        "channels, and permutes D29's eight command channels. The exact .009",
        "D29 row transcription is in `ref/schematics/d29-exact-009-pinmap-review.json`;",
        "the guard compares the command rows with fixed expectations transcribed",
        "from that review; it does not read or hash the review file. Other checked",
        "pad endpoints and per-instance LVS maps use ordered logical buses.",
        "Factory sheets 1 and 3 prove that D100 instead buffers eight",
        "floppy-drive outputs. Its paired channels and separate pin-9 OE_N and",
        "pin-11 T nets are guarded independently of the data-bus devices.", "",
        "Primary pinout source:",
        "`https://www.silicon-ark.co.uk/datasheets/m8286-m8287-datasheet-intel.pdf`", "",
        "## Command", "",
        "Run from the repository root with Python 3 (standard library only).",
        "The command overwrites this report with the check results, including failures,",
        "then exits nonzero if any check fails.", "", "```sh",
        "python3 scripts/report_8286_pinout_audit.py", "```", "",
        "## Checks", "", "| Check | Result |", "| --- | --- |",
    ]
    lines.extend(f"| {name} | {'PASS' if ok else 'FAIL'} |" for name, ok in checks)
    lines.extend([
        "", "## Scope", "",
        "This guard compares the listed main-board source contracts, net endpoints",
        "and LVS mapping data with fixed pinout/channel expectations. It does not",
        "run LVS, inspect routed copper, simulate turnaround timing or measure",
        "physical continuity. D100 control and remote-source boundaries remain",
        "subject to the [FDC handoff](fdc-hardware-handoff.md).",
    ])
    OUT.write_text("\n".join(lines) + "\n")
    print(f"Wrote {OUT.relative_to(ROOT)}")
    if failed:
        raise SystemExit("8286 PINOUT AUDIT: FAIL: " + "; ".join(failed))
    print("8286 PINOUT AUDIT: PASS")


if __name__ == "__main__":
    main()
